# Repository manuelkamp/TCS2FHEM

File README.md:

# TCS2FHEM

If you have a TCS:Bus door intercom system and want to integrate it into your FHEM instance, this is a project for you. The goal of this project is to have a device, that connects the TCS:Bus intercom to FHEM. It should allow to trigger the dooropener and other functions (such as switching on the light) in FHEM. Also it should send events (like someone ringed the bell at the front door, or someone ringed the bell at the main door) to FHEM, so you can automate it (send notifications, interact...)  
## ATTENTION: THIS REPOSITORY IS A COPY AND WILL NOT BE UPDATED ON REGULAR BASIS. PLEASE GO TO https://git.kmpr.at/kamp/TCS2FHEM TO SEE THE LATEST CODE AND/OR SUBMIT PULL REQUESTS OR ISSUES!

## Hardware  
* [Raspberry Pico W](https://mk0.at/pico-w)  
* [Waveshare 2,23" OLED Display](https://mk0.at/waveshare-oled)  
* [4-Button Keypad](https://mk0.at/4-keypad)  
* PCB for your need (see kicad folder for examples)  
* 3D-printed Custom Case for Pico and Button Keypad and power circuit (see case_5v_PCB folder as an example)  

## Prereqisites
You need your PCB fully soldered with everything (you can use a Breadboard temporarily), including keypad and display. Load the Micropython firmware onto your Pico W. I used the v1.19.1-782-g699477d12 (2022-12-20).uf2. It is highly recommended to load the newest firmware from the official repository: https://micropython.org/download/rp2-pico-w/ - But you can use the one I used too, see firmware folder in this repository. Then upload all *.py files to the Pico W's root path (follow the instructions for configuration) and connect the TCS Bus lines accordingly. Finally plug in power (if not powered by TCS:Bus).

## Instructions/Setup
In the file configs.py set your configurations:  
country: your countrycode (AT=Austria, DE=Germany...) (2-digit string)  
ntp_host: set a ntp server (string url)  
gmt_offset: offset to gmt for your timezone in hours (int)  
auto_summertime: Enables changing to summertime (and back) automatically (True/False)  
disable_wifi_powersavingmode: Wifi powersavingmode is enabled per default. Set to true to disable powersavingmode for Wifi (True/False)  
api_port: Port on which the API is available (int)  
displayoff: Minutes after last action, display goes off automatically (int)  
log_incoming_bus_messages: Logs every incoming bus message, which is useful to find out relevant messages for initial setup (bool)  
log_housekeeping_days: Logfiles older than this value in days get deleted by housekeeping (int)  
frontdoor_ringing_message: The TCS:Bus message if someone rings the front door (list)  
door_ringing_message: The TCS:Bus message if someone rings the door (list)  
door_trigger_message: The TCS:Bus message to trigger the front door opener (list)  
light_trigger_message: The TCS:Bus message to trigger the light (list)  
tcs_message: The TCS:Bus message sent every 37 minutes from the TCS:Bus device to check devices - no action, just for filtering (list)  
api_client_ip: Only this IP is allowed to use the API. Leave blank to allow all connections from all IPs (string)  
fhem_door_ringed: URL of FHEM command, when the door is ringed (string)  
fhem_frontdoor_ringed: URL of FHEM command, when the front door is ringed (string)  

In the file secrets.py set your configurations:  
ssid: Wifi name (string)  
pw: Wifi password (string)  
api: API key (string)  

**Hint:** use `openssl rand -hex 20` to generate the api_key

## Wiring of Display  
```
OLED   =>    Pico  
VCC    ->    VSYS  
GND    ->    GND  
DIN    ->    11  
CLK    ->    10  
CS     ->    9  
DC     ->    8  
RST    ->    12  
SDA    ->    6  
SCL    ->    7   
```

## Wiring of 4-Button Keypad  

## Power circuit  
### Power from TCS Bus  
The power circuit allows you to run the Pico W directly from the TCS:Bus system's power. It also connects the bus to the Pico to read and write from it. The circuit files for KiCad are stored in the kicad subfolder 'power_from_tcs_bus' of this repo. You can order/print your own PCB with that files.  

### Power from 5V power source
The power circuit allows you to run the Pico W with a separate 5 Volt power source (f.e. a USB power adapter). It also connects the bus to the Pico to read and write from it. The circuit files for KiCad are stored in the kicad subfolder 'power_via_5v_source' of this repo. You can order/print your own PCB with that files.  

### Power from 9-24V power source
The power circuit allows you to run the Pico W with a separate power source from 9 Volt to 24 Volt. It also connects the bus to the Pico to read and write from it. The circuit files for KiCad are stored in the kicad subfolder 'power_via_9-24v_source' of this repo. You can order/print your own PCB with that files.  

## Networking  
Be sure that you give your Pico a static IP address on your router, so you know where the webservice is available and can set it up in FHEM.

## TCS2FHEM API  
You can configure the port, on which the API runs in configs.py in the 'api_port'-value. You also have to set an API-Key in secrets.py in the 'api'-value. Then you can call the API as follows:  
http://servername/api_key/command[/json]  

You can use the following commands:  
triggerdoor - Triggers the front door opener  
triggerlight - Triggers the light  
togglepartymode - Enables/disables the Party-Mode  
partymodeon - Sets Party-Mode enabled  
partymodeoff - Sets Party-Mode disabled  
partymodestate - Returns the state of the Party-Mode  
ping - Check if the API is up and running  
stats - Returns some stats of the device  
reboot - Reboots the device  
ringdoor - Sends "ring doorbell" message to TCS:Bus  
ringfrontdoor - Sends "ring front doorbell" message to TCS:Bus  

## FHEM API  

With the FHEM API you interconnect your FHEM instance with your TCS2FHEM device. It allows you for example control the door trigger via FHEM, or handle incoming TCS:Bus messages within FHEM to send you a notification or anything else. In this example configuration, we set up a HTTPMOD device in FHEM to control your TCS2FHEM device within FHEM, using the above explained API commands.  

### Example Setup of FHEMWEB

You need to give your TCS2FHEM device a static IP address within your network. Then you need to create a new FHEMWEB and configure it to work only with the static IP of your TCS2FHEM device without the csrfToken.  

```
define WEBapi FHEMWEB 8086 global
attr WEBapi csrfToken none
attr WEBapi allowfrom your-TCS2FHEM-static-IP|127.0.0.1
```

### Exampe of a HTTPMOD device in FHEM to control TCS2FHEM

This device is used to trigger actions from FHEM via the TCS2FHEM API. In this Example you can trigger the dooropener, the light and the builtin partymode of the TCS2FHEM device.  

```
define TCS2FHEM HTTPMOD 0
setuuid TCS2FHEM 63b875f4-f33f-1b7d-61d3-9101ee190fa5bae1
attr TCS2FHEM icon Todoist
attr TCS2FHEM room TCS
attr TCS2FHEM set01Name triggerDoor
attr TCS2FHEM set01NoArg 1
attr TCS2FHEM set01URL http://servername/api_key/triggerdoor
attr TCS2FHEM set02Name triggerLight
attr TCS2FHEM set02NoArg 1
attr TCS2FHEM set02URL http://servername/api_key/triggerlight
attr TCS2FHEM set03Name togglePartyMode
attr TCS2FHEM set03NoArg 1
attr TCS2FHEM set03URL http://servername/api_key/togglepartymode
attr TCS2FHEM webCmd triggerDoor:triggerLight:togglePartyMode
```

### Example of Notify and Dummy device in FHEM to send a message to your smartphone

This dummy device is used to represent the state. The state 'idle' means, there is no action. The state 'ringed' is set if someone rings your doorbell and the TCS2FHEM device sets it. The notify device in FHEM is used to see the change from idle to ringed, and you can perform your wanted action in FHEM.  

```
define TCS_Door dummy
setuuid TCS_Door 63a1c02e-f33f-1b7d-29b2-21917943a9d12101
attr TCS_Door room TCS
attr TCS_Door setList idle ringed
```

```
define n_TCS_Door notify TCS_Door:ringed set Talk msg Jemand hat an der Wohnungstür angeläutet;; set TCS_Door idle
setuuid n_TCS_Door 63a1c0c2-f33f-1b7d-fe89-1e89dde293580eb1
attr n_TCS_Door disabledAfterTrigger 10
attr n_TCS_Door room TCS
```

For this devices, the FHEM API Url that you need to use in TCS2FHEM setting 'fhem_door_ringed' would be:  
```
http://fhem-server:8086/fhem?cmd=set%20TCS_Door%20ringed&XHR=1
```

This works exactly the same for the TCS2FHEM settings 'fhem_frontdoor_ringed'.

### Example of Notify and Dummy device in FHEM for Partymode

If you decide to not use the builtin Partymode in your TCS2FHEM device, you can set up a Partymode in FHEM. This may be useful, if you want to trigger more actions as it would be possible with just the TCS2FHEM device.  

```
coming soon...
``` 

## Legal remarks
I am not affiliated to TCSAG and/or any of their brands and/or trademarks, nor do I have any business information on the proprietary TCS:Bus. I just reverse engineered it, to include my intercom system into my home automation and shared my research here. All Rights to the possible Trademark TCS:Bus and all things connected, remain untouched by this open source project.

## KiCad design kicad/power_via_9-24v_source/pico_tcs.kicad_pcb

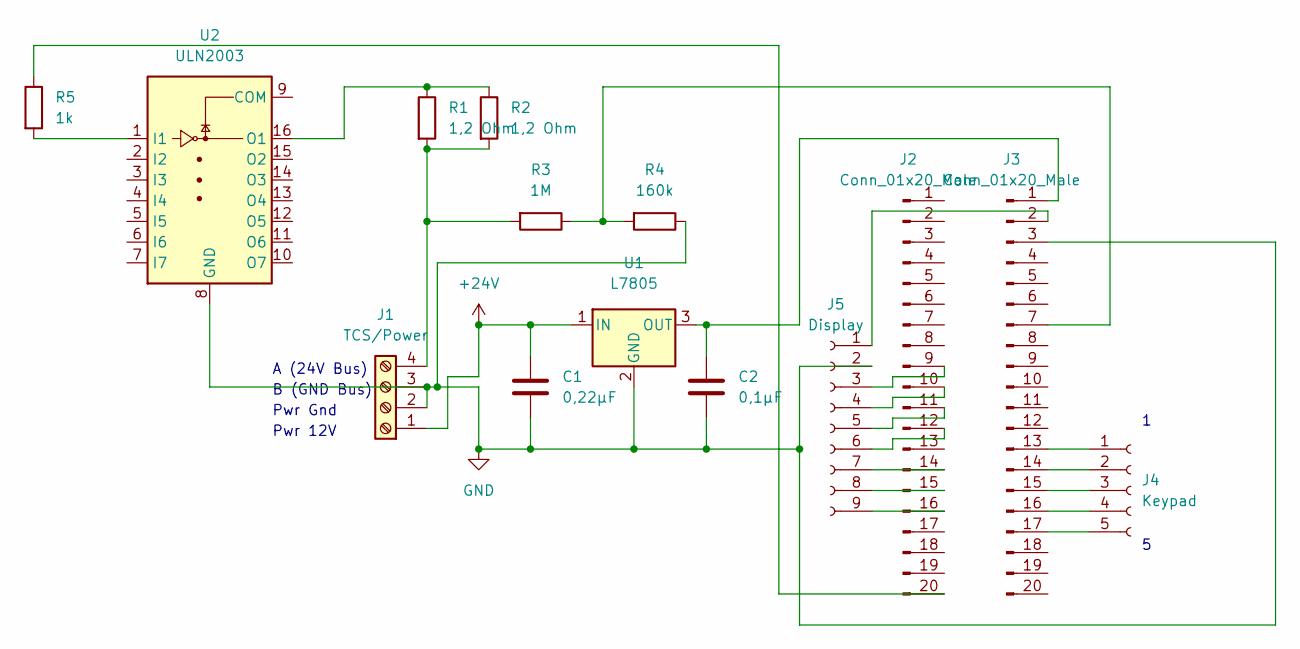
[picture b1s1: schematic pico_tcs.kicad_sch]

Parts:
C1: 0,22µF; C_Disc_D6.0mm_W4.4mm_P5.00mm
C2: 0,1µF; C_Disc_D6.0mm_W4.4mm_P5.00mm
J1: TCS/Power; TerminalBlock_MetzConnect_Type011_RT05504HBWC_1x04_P5.00mm_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
J2, J3: Conn_01x20_Male; PinSocket_1x20_P2.54mm_Vertical
J4: Keypad; PinHeader_1x05_P2.54mm_Vertical
J5: Display; PinSocket_1x09_P2.54mm_Vertical
R1, R2: 1,2 Ohm; R_Axial_DIN0207_L6.3mm_D2.5mm_P10.16mm_Horizontal
R3: 1M; R_Axial_DIN0207_L6.3mm_D2.5mm_P10.16mm_Horizontal
R4: 160k; R_Axial_DIN0207_L6.3mm_D2.5mm_P10.16mm_Horizontal
R5: 1k; R_Axial_DIN0207_L6.3mm_D2.5mm_P10.16mm_Horizontal
U1: L7805; TO-218-3_Vertical
U2: ULN2003; DIP-16_W7.62mm

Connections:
+24V: C1.1, J1.1, U1.1 (IN)
GND: C1.2, C2.2, J1.2, J1.3, J3.3, J5.2, R4.1, U1.2 (GND), U2.8 (GND)
unnamed: C2.1, J3.1, U1.3 (OUT)
unnamed: J1.4, R1.2, R2.2, R3.2
unnamed: J2.9, J5.3
unnamed: J2.10, J5.4
unnamed: J2.11, J5.5
unnamed: J2.12, J5.6
unnamed: J2.14, J5.7
unnamed: J2.15, J5.8
unnamed: J2.16, J5.9
unnamed: J2.20, R5.1
unnamed: J3.2, J5.1
unnamed: J3.7, R3.1, R4.2
unnamed: J3.13, J4.1
unnamed: J3.14, J4.2
unnamed: J3.15, J4.3
unnamed: J3.16, J4.4
unnamed: J3.17, J4.5
unnamed: R1.1, R2.1, U2.16 (O1)
unnamed: R5.2, U2.1 (I1)

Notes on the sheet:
Pwr Gnd
Pwr 12V
A (24V Bus)
B (GND Bus)

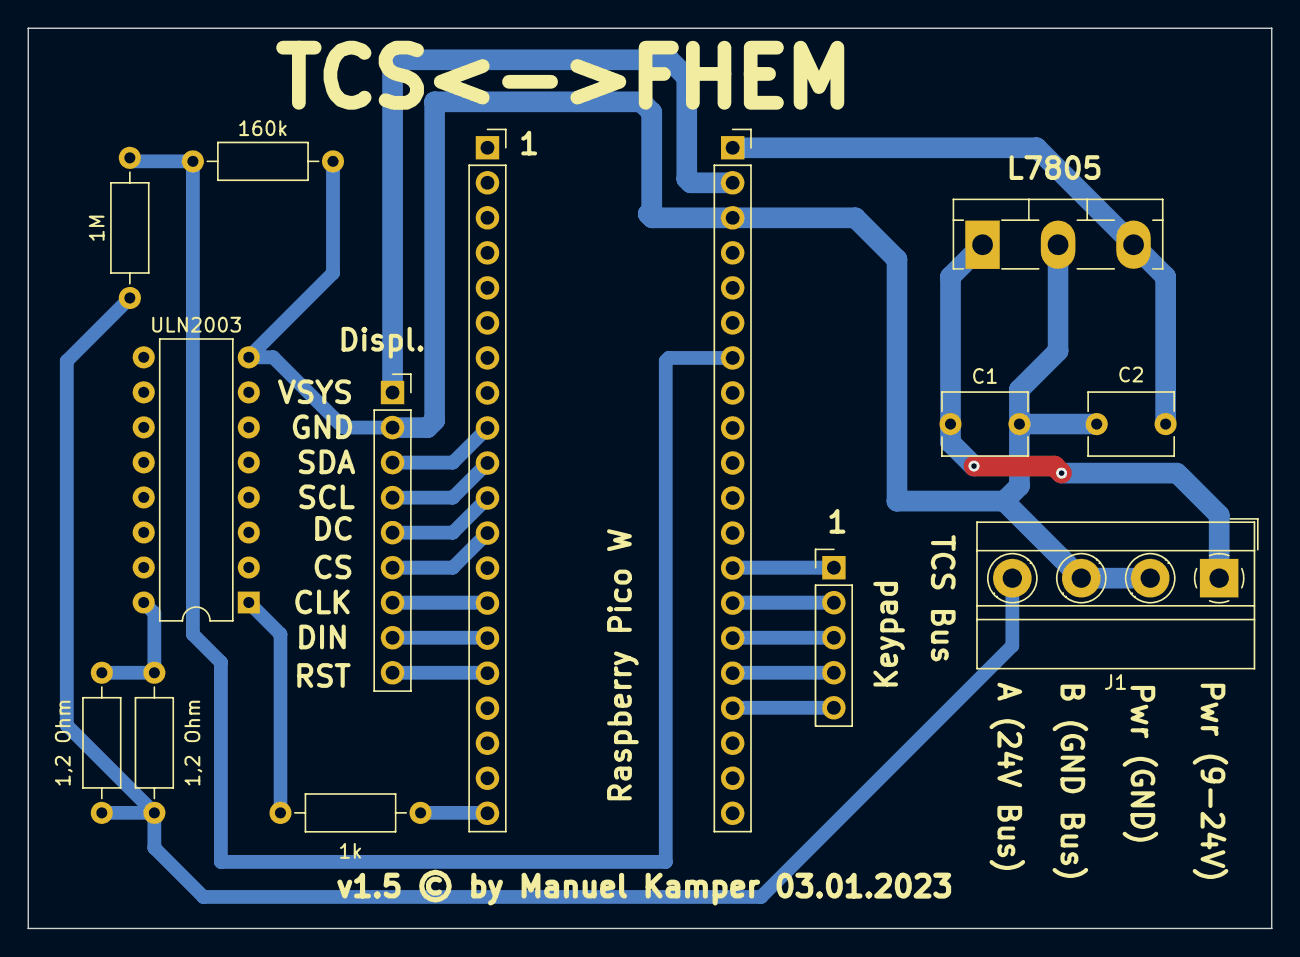
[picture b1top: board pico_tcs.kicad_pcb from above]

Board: 2 copper layers, 90.2 x 65.3 mm, 14 parts (0 on the bottom side), 21 nets.

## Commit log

2022-12-11 „README.md“ ändern
2022-12-12 Dateien hochladen nach „docs“
2022-12-12 Dateien hochladen nach „“
2022-12-12 Dateien hochladen nach „“
    implemented #5
2022-12-17 Dateien hochladen nach „kicad“
2022-12-18 „secrets.py“ ändern
2022-12-20 „docs/pico_tcs.png“ löschen
2022-12-20 „kicad/pico_tcs.kicad_sch“ löschen
2022-12-20 „kicad/pico_tcs.kicad_pro“ löschen
2022-12-20 „kicad/pico_tcs.kicad_prl“ löschen
2022-12-20 „kicad/pico_tcs.kicad_pcb“ löschen
2022-12-20 „kicad/fp-info-cache“ löschen
2022-12-20 Dateien hochladen nach „kicad/power_from_tcs_bus“
2022-12-20 Dateien hochladen nach „kicad/power_via_5v_source“
2022-12-20 Dateien hochladen nach „kicad/power_via_9-24v_source“
2023-01-03 Dateien hochladen nach „kicad/power_from_tcs_bus“
    fixed bug in connection between display and pico
2023-01-03 fixed bug in connection between display and pico
2023-01-03 Dateien hochladen nach „firmware“
2023-01-03 fixed #18
    create folder "logs" if it does not exist
2023-01-03 case_5v_pcb
2023-01-03 „case_base.stl“ löschen
2023-01-03 „case_plate.stl“ löschen
2023-01-03 Dateien hochladen nach „case_5v_PCB“
2023-01-04 improved plate with display holder and relocated keypad-hole and thicker case-walls
2023-01-04 improved case base
2023-01-04 reversed keypad button order to fit new case design (keypad upside down)
2023-01-04 implemented #20
2023-01-04 implemented #15
2023-01-04 implemented #19
2023-01-05 implemented #21 and #22
2023-01-05 fixed #25
2023-01-05 implemented #27
2023-01-05 implemented #24
2023-01-05 implemented #26
2023-01-06 implemented basic bus reader #13
    missing triggering of external api
2023-01-06 implemented #17
2023-01-06 implemented #4
2023-01-06 implemented #14
2023-01-06 implemented #32
2023-01-06 implemented #31
2023-01-06 fixed #34

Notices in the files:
kicad/power_via_9-24v_source/pico_tcs.kicad_pcb:
v1.5 © by Manuel Kamper 03.01.2023
